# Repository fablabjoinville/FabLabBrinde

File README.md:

# Lâmpada Relâmpago — Kit Comemorativo 10 Anos Fab Lab Joinville

Uma versão curta e alegre do projeto: uma nuvem, um relâmpago e um pouco de mágica magnética.

_O esboço que eu e o Segui fizemos — foi assim que começou._

Como funciona (resumo):

- Ímãs se atraem e puxam a peça móvel.
- A PCB flexiona e aciona o switch (click!).
- LEDs tipo "string" acendem, iluminando a nuvem e o relâmpago.
O que tem aqui:

- Arquivos KiCad e gerbers para a PCB
- Vetores CNC para a base
- Modelos 3D para nuvem e relâmpago
Dicas rápidas:

- Verifique a profundidade do alojamento do switch se não houver clique.
- Teste os LEDs antes da montagem final.

Contribuições e melhorias são bem-vindas — faça brilhar! ✨
Licença: open-source (maker-friendly).
# Lâmpada Relâmpago — Kit Comemorativo 10 Anos Fab Lab Joinville

Parabéns — você encontrou um pedaço do trovão! Este repositório guarda tudo que você precisa para fabricar e montar a lâmpada relâmpago do aniversário de 10 anos do Fab Lab Joinville. É um presente que brilha, faz "click" e pode provocar sorrisos.

## Imagens (porque todo projeto merece glamour)

- Esboço do conceito: ./Docs/Scanned.jpg
- Render da placa: ./Docs/pcb_render.jpg

## Em poucas palavras (sem jargões chatos)

Imagine uma nuvem fofinha que guarda um segredo elétrico e um relâmpago que, quando aproximado, faz a nuvem piscar como se tivesse contado uma piada muito boa. Dois ímãs se apaixonam, a placa dá um suspiro elástico, o interruptor faz "click" e os LEDs dançam em azul.

Como funciona, versão curta e dramática:

1. Os ímãs da nuvem e do relâmpago se atraem (romance magnético).
2. A PCB flexiona levemente e ativa o switch (o gran finale do drama).
3. LEDs tipo "string" acendem, iluminando a nuvem e o relâmpago.

## O que vem no kit (ou nesta pasta)

- Arquivos KiCad e gerbers para a placa (PCB).
- Vetores para CNC da base de madeira.
- Modelos 3D para impressão da nuvem e do relâmpago.
- Documentação e imagens no diretório `Docs`.

## Ferramentas e materiais (a lista do faz-tudo)

- Fresadora CNC (para a base)
- Impressora 3D (para as peças decorativas)
- Estação de solda e estanho
- Ímãs de neodímio (pequenos, mas poderosos)
- Fios e conector JST para alimentação
- LEDs tipo "string" (azuis recomendados)

## Montagem — passo a passo para heróis e heroínas

1. Fresagem da base: corte o alojamento para o switch com cuidado para permitir o clique quando a PCB flexiona.
2. Monte a PCB: solde o switch detector (KFC-V-105-2), o conector JST e os fios dos LEDs.
3. Prenda os ímãs: cole nos locais indicados na nuvem e no relâmpago. Verifique a polaridade — a atração é essencial.
4. Teste rápido: ligue os LEDs antes de montar tudo para garantir que a fiação está certa.
5. Montagem final: encaixe a PCB na base, coloque a nuvem por cima e passe o relâmpago pela abertura.
6. Aproxime o relâmpago da nuvem — e voilà, faça seu pedido (ou só admire a luz).

## Créditos e agradecimentos

Obrigado ao Fab Lab Joinville pela inspiração e por deixar a imaginação virar protótipo. Projeto colaborativo — contribuições são bem-vindas!

## Licença

Open-source e maker-friendly. Compartilhe, modifique e faça brilhar — com amor e responsabilidade.

— Equipe Fab Lab Joinville

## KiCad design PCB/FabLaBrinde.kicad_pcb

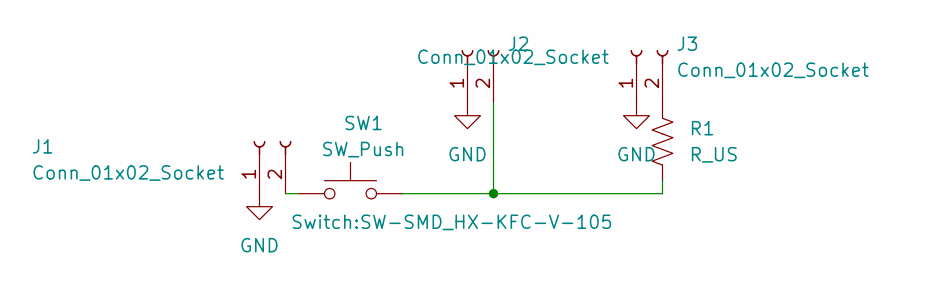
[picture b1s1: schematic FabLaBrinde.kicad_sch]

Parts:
J1, J2, J3: Conn_01x02_Socket; JST_PH_B2B-PH-K_1x02_P2.00mm_Vertical
R1: R_US; R_Axial_DIN0204_L3.6mm_D1.6mm_P5.08mm_Horizontal
SW1: SW_Push; SW-SMD_HX-KFC-V-105

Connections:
GND: J1.1, J2.1, J3.1
unnamed: J1.2, SW1.1
unnamed: J2.2, R1.2, SW1.2
unnamed: J3.2, R1.1

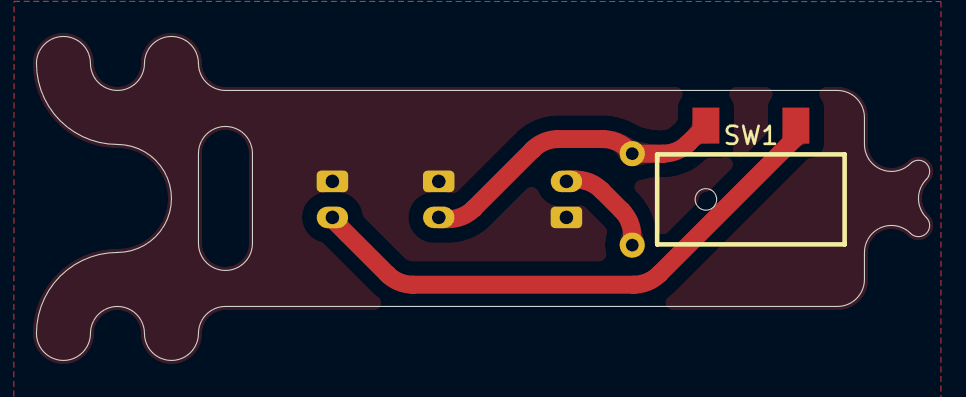
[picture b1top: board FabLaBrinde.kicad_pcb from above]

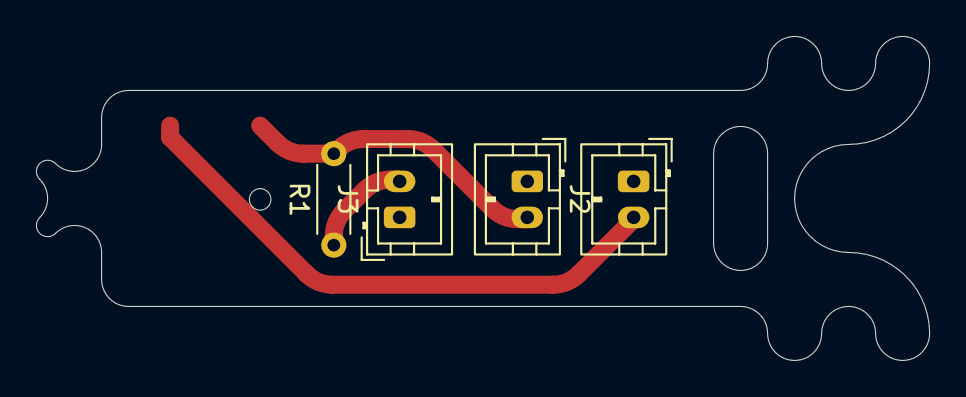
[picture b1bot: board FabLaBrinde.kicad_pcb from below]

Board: 2 copper layers, 49.6 x 18.0 mm, 5 parts (4 on the bottom side), 4 nets.

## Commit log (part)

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2026-05-22 Updt BOM
